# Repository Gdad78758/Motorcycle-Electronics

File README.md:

# Motorcycle-Electronics
Motorcycle electronics projects repository

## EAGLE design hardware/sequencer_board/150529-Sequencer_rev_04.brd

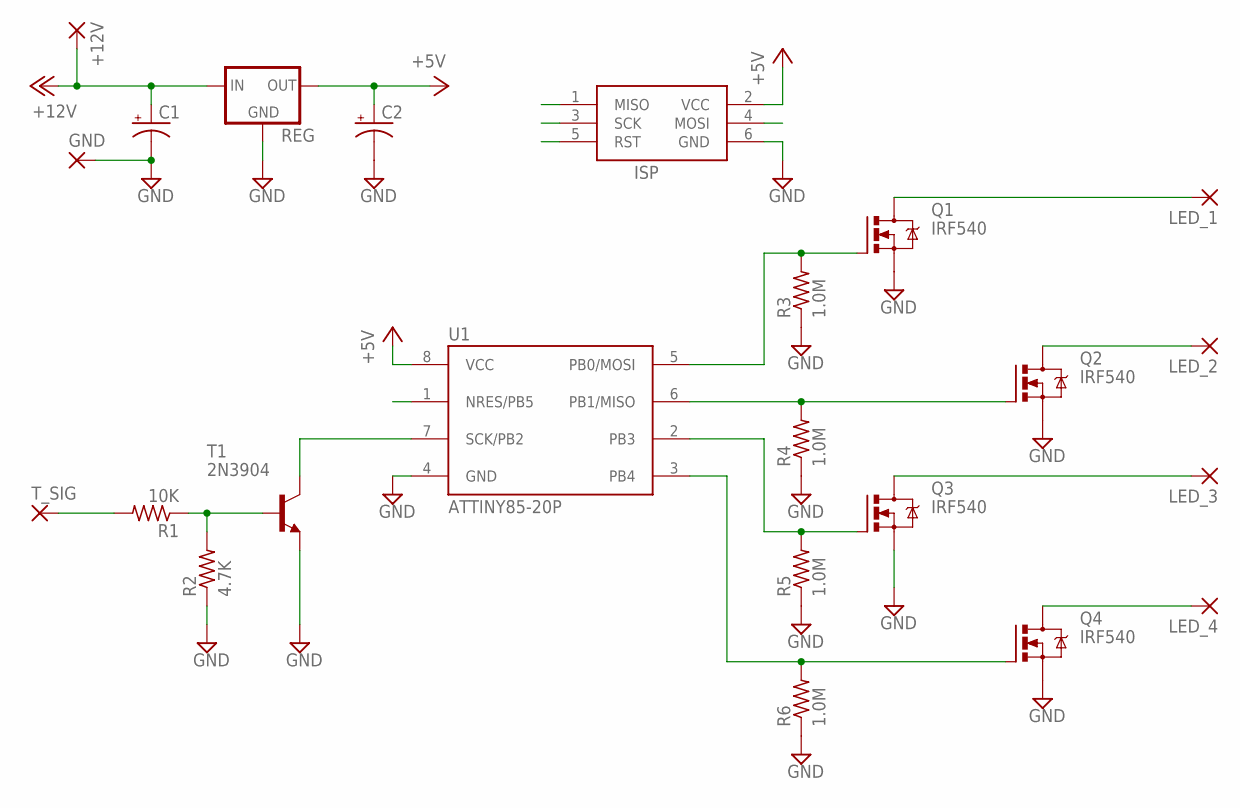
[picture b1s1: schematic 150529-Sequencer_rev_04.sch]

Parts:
+12V: 1,6/0,8
C1, C2: CPOL-USE5-10.5; E5-10,5
GND: 1,6/0,8
ISP: AVRISP-6; AVRISP
LED_1, LED_2, LED_3, LED_4: 1,6/0,8
Q1, Q2, Q3, Q4: IRF540; TO220BV
R1: 10K; 0207/2V
R2: 4.7K; 0207/2V
R3, R4, R5, R6: 1.0M; 0207/2V
REG: 78XXS
T1: 2N3904; TO92
T_SIG: 1,6/0,8
U1: ATTINY85-20P; PDIP08_300MIL

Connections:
+5V: C2.+, ISP.2 (VCC), REG.OUT, U1.8 (VCC)
+12V: +12V.1, C1.+, REG.IN
GND: C1.-, C2.-, GND.1, ISP.6 (GND), Q1.S, Q2.S, Q3.S, Q4.S, R2.1, R3.1, R4.1, R5.1, R6.1, REG.GND, T1.3 (E), U1.4 (GND)
LED_1: LED_1.1, Q1.D
LED_2: LED_2.1, Q2.D
LED_3: LED_3.1, Q3.D
LED_4: LED_4.1, Q4.D
unnamed: R1.1, R2.2, T1.2 (B)
NRES/PB5: ISP.5 (RST), U1.1 (NRES/PB5)
PB0/MOSI: ISP.4 (MOSI), Q1.G, R3.2, U1.5 (PB0/MOSI)
PB1/MISO: ISP.1 (MISO), Q2.G, R4.2, U1.6 (PB1/MISO)
PB3: Q3.G, R5.2, U1.2 (PB3)
PB4: Q4.G, R6.2, U1.3 (PB4)
SCK/PB2: ISP.3 (SCK), T1.1 (C), U1.7 (SCK/PB2)
T_SIG: R1.2, T_SIG.1

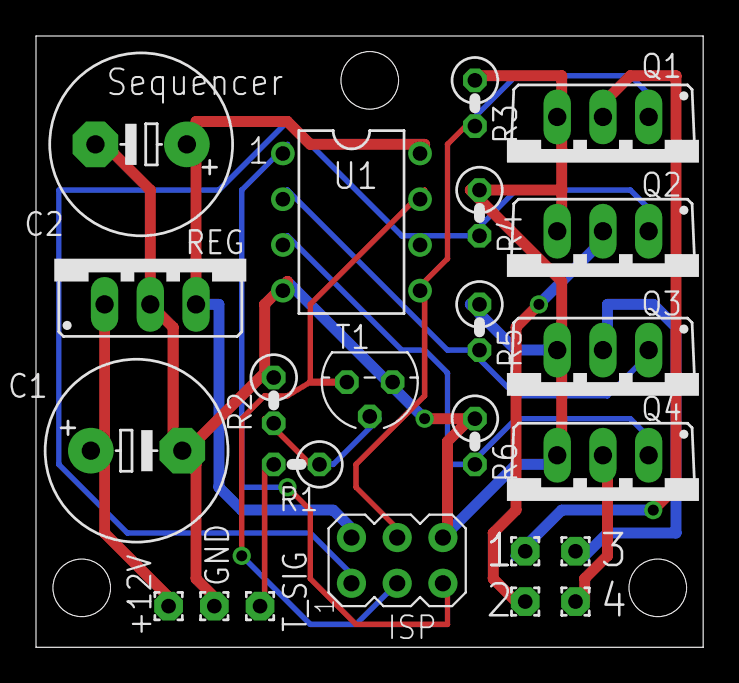
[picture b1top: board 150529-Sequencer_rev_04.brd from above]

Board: 2 copper layers, 37.1 x 34.0 mm, 23 parts (0 on the bottom side), 15 nets.

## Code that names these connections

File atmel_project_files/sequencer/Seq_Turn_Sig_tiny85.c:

/*
 * $safeprojectname$.c
 *
 * Created: 5/15/2015 3:06:46 PM
 *  Author: Roger
 */ 

 
//********** Includes **********

#define F_CPU  1000000UL
#include <avr/io.h>     
#include <util/delay.h>   
#include <avr/interrupt.h>

//********** Definitions **********

// LED Segment Control Outputs

#define Segment1   PB0
#define Segment2   PB1
#define Segment3   PB3
#define Segment4   PB4
#define IO_PORT  PORTB
#define IO_DDR   DDRB


// Turn Signal Control Input Pin

#define TS_SWITCH   PINB2   // bit is clear when turn signal is activated
#define TS_SWITCH_PORT PINB


//********** Function Prototypes **********

void setup( void );
void ts_seq();
void marker_light();


//********** Global Variables **********

volatile uint32_t  timestamp = 0;
volatile uint32_t  old_timestamp = 0;
volatile uint32_t  time_period = 0;
volatile uint8_t   timeout = 0;

/*
ISR(INT0_vect)
{
	timeout = 0;
	TCNT1 = 0x00;
	
}

ISR(TIMER1_OVF_vect)
{
	if (bit_is_clear(TS_SWITCH_PORT, TS_SWITCH))
	{
		marker_light(); 
	}
}
*/


int main(void)
{


setup();



 while(1)
 { 
  
  
  while (bit_is_clear(TS_SWITCH_PORT, TS_SWITCH))
	{  
		ts_seq();  
	}
  
  
  while(bit_is_set(TS_SWITCH_PORT, TS_SWITCH))
	{
		//marker_light();	
	}
  
       
 }
}


//********** Functions **********

void setup(void)
{

 //********* Port Config *********

IO_DDR |= (1 <<Segment4) | (1<<Segment3) | (1<<Segment2) | (1<<Segment1);  // set led segment control pins to "1" for output 
IO_PORT &= ~((1 <<Segment4) | (1<<Segment3) | (1<<Segment2) | (1<<Segment1));   // turn the led segments off

IO_DDR &= ~( 1 << TS_SWITCH );   // set TS_SWITCH pin to 0 for input
//IO_PORT |= ( 1 << TS_SWITCH );   // write a 1 to TS_SWITCH to enable the internal pullup

 //**********Interrupt Enable***************
 
TCCR1 &= ~((1<<CS13) | (1<<CS12) | (1<<CS11) | (1<<CS10));
//TIMSK |= 1<<TOIE1; 
//GIMSK |= 1<<INT0;	// Enable INT0 (input pin B2) 
//MCUCR |= (1<<ISC01) | (1<<ISC00);	// Trigger INT0 on rising edge
//sei();				//Enable Global Interrupts
}


void marker_light()
{
 
	 // low intensity marker light sequencing loop
	 
	 uint16_t on_delay = 100; // delay after turn on
	 uint16_t off_delay = 1000; // delay after turn off
	 
	 IO_PORT |= (1<<Segment4) | (1<<Segment3) | (1<<Segment2) | (1<<Segment1);
	 _delay_us(on_delay);
	 IO_PORT &= ~((1<<Segment4) | (1<<Segment3) | (1<<Segment2) | (1<<Segment1));
	 _delay_us(off_delay);
   
}   

void ts_seq()

{
	uint16_t delay_between_seq = 233; // delay between segments
	uint16_t delay_after_seq = 233; //delay after segments shutoff
	
	//  create the turn signal sequencing with delays between segments

	IO_PORT |= (0<<Segment4) | (0<<Segment3) | (0<<Segment2) | (1<<Segment1);
	_delay_ms(delay_between_seq);
	IO_PORT |= (0<<Segment4) | (0<<Segment3) | (1<<Segment2) | (1<<Segment1);
	_delay_ms(delay_between_seq);
	IO_PORT |= (0<<Segment4) | (1<<Segment3) | (1<<Segment2) | (1<<Segment1);
	_delay_ms(delay_between_seq);
	IO_PORT |= (1<<Segment4) | (1<<Segment3) | (1<<Segment2) | (1<<Segment1);
	_delay_ms(delay_between_seq);
	IO_PORT &= ~((1<<Segment4) | (1<<Segment3) | (1<<Segment2) | (1<<Segment1));
	_delay_ms(delay_after_seq);
}

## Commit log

2015-07-02 Create MLP Branch Readme
2015-07-02 adding ignore file
2015-07-02 this is a test if deleting a document
2015-07-09 Added scope trace with mech relay
2015-07-17 Loading sequencer board and code, and turn signal board and code
2015-07-18 Delete 150717-TS_Sequencer_MLP_revXX.c
    This file was repeated under the Atmel folder
2015-07-19 Uploading sequencer files as of 150718
2015-07-19 Second set of sequencer files added 150719
